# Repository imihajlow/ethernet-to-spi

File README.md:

# An experiment project to receive and decode a 10BASE-T Ethernet signal

The Nucleo64 shield schematic files are located in sch/shield/.

The firmware for stm32f401 is located in stm32eth-f401/.

## Receiver operation

The idea is to convert the Manchester-encoded 10BASE-T signal to SPI and use an STM32 MCU to parse it.

A 75C1168 chip is used to convert differential signals to 5V logic levels.

Then, edges are detected using a 74HC86 XOR.

*Blue is the input signal, yellow - detected edges.*

Then, an `~idle` signal is formed using a delay circuit. It goes from 0 to 1 with the first edge and goes back to 0 after approximately 2 µS after the last transition. This signal is used by the MCU to detect the end of an Ethernet frame.

When the line is idle, the output of an 75C1168 is undefined. In my case it was always high. Since the Ethernet frame always starts with a pattern of 101010..., this leads to the first transition always being from 1 to 0, which generates the first edge. This edge must be ignored for SPI clock generation. However, the case with a low idle state needs to be handled as well. In that case the line remains low on the frame begin and the first edge should not be ignored.

The filtering of the first edge is done using the already generated `~idle` signal.

*First edge is filtered*

The resulting filtered edge signal is fed onto a non-retriggerable monostable circuit which generates a pulse of approximately 75 nS, which is finally used as an SPI clock.

*Blue - generated SPI SCK signal, yellow - SPI MOSI which is just the input 10BASE-T signal.*

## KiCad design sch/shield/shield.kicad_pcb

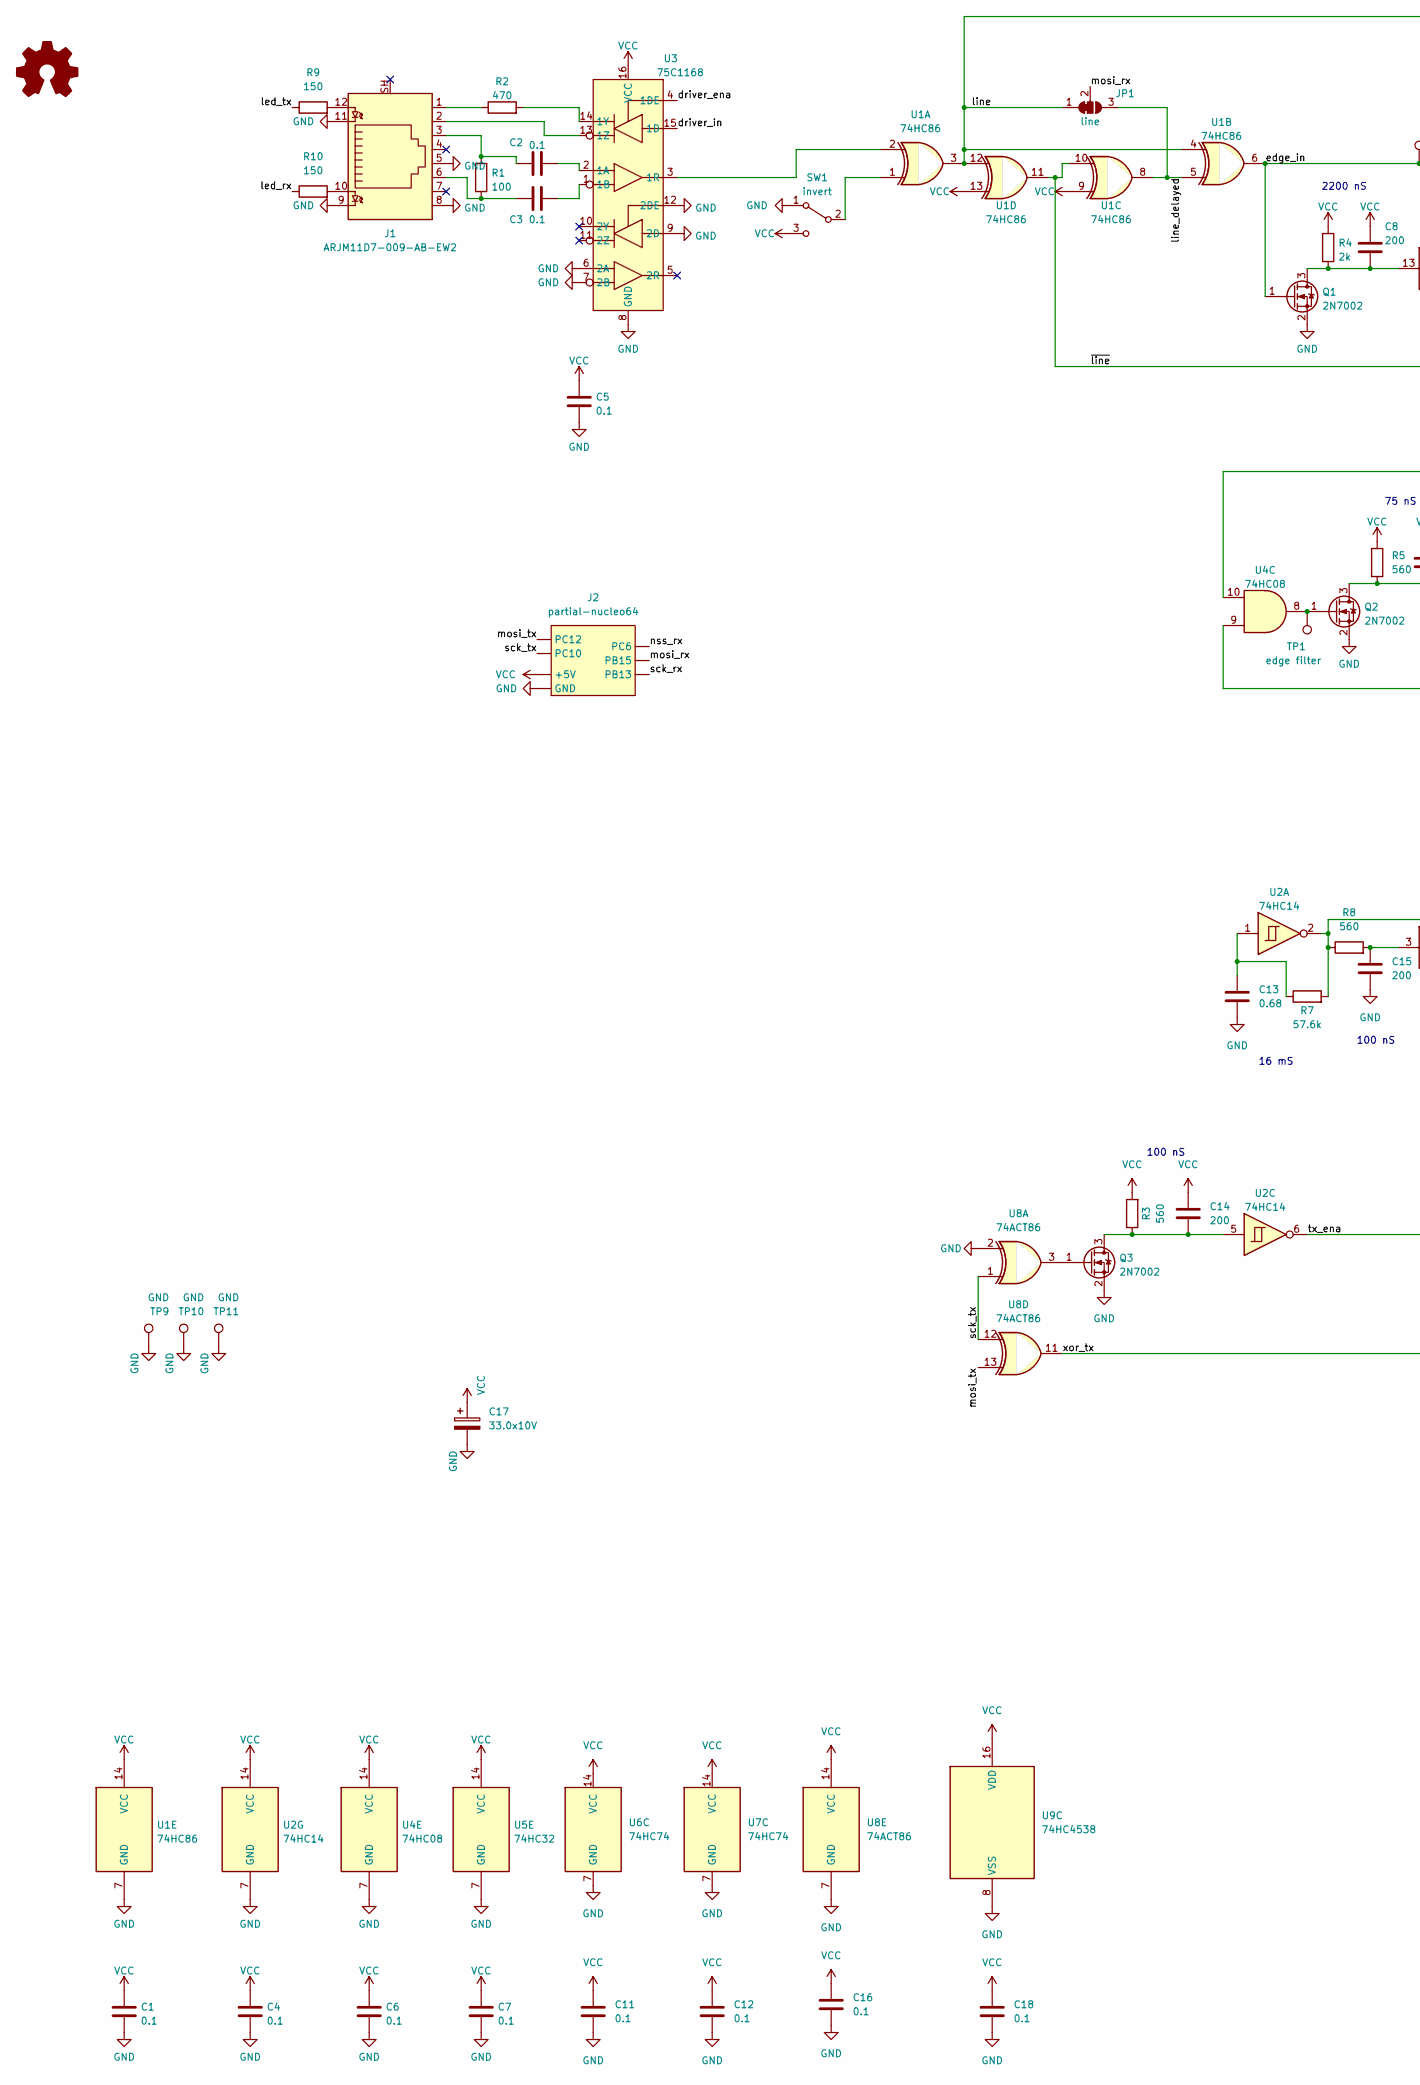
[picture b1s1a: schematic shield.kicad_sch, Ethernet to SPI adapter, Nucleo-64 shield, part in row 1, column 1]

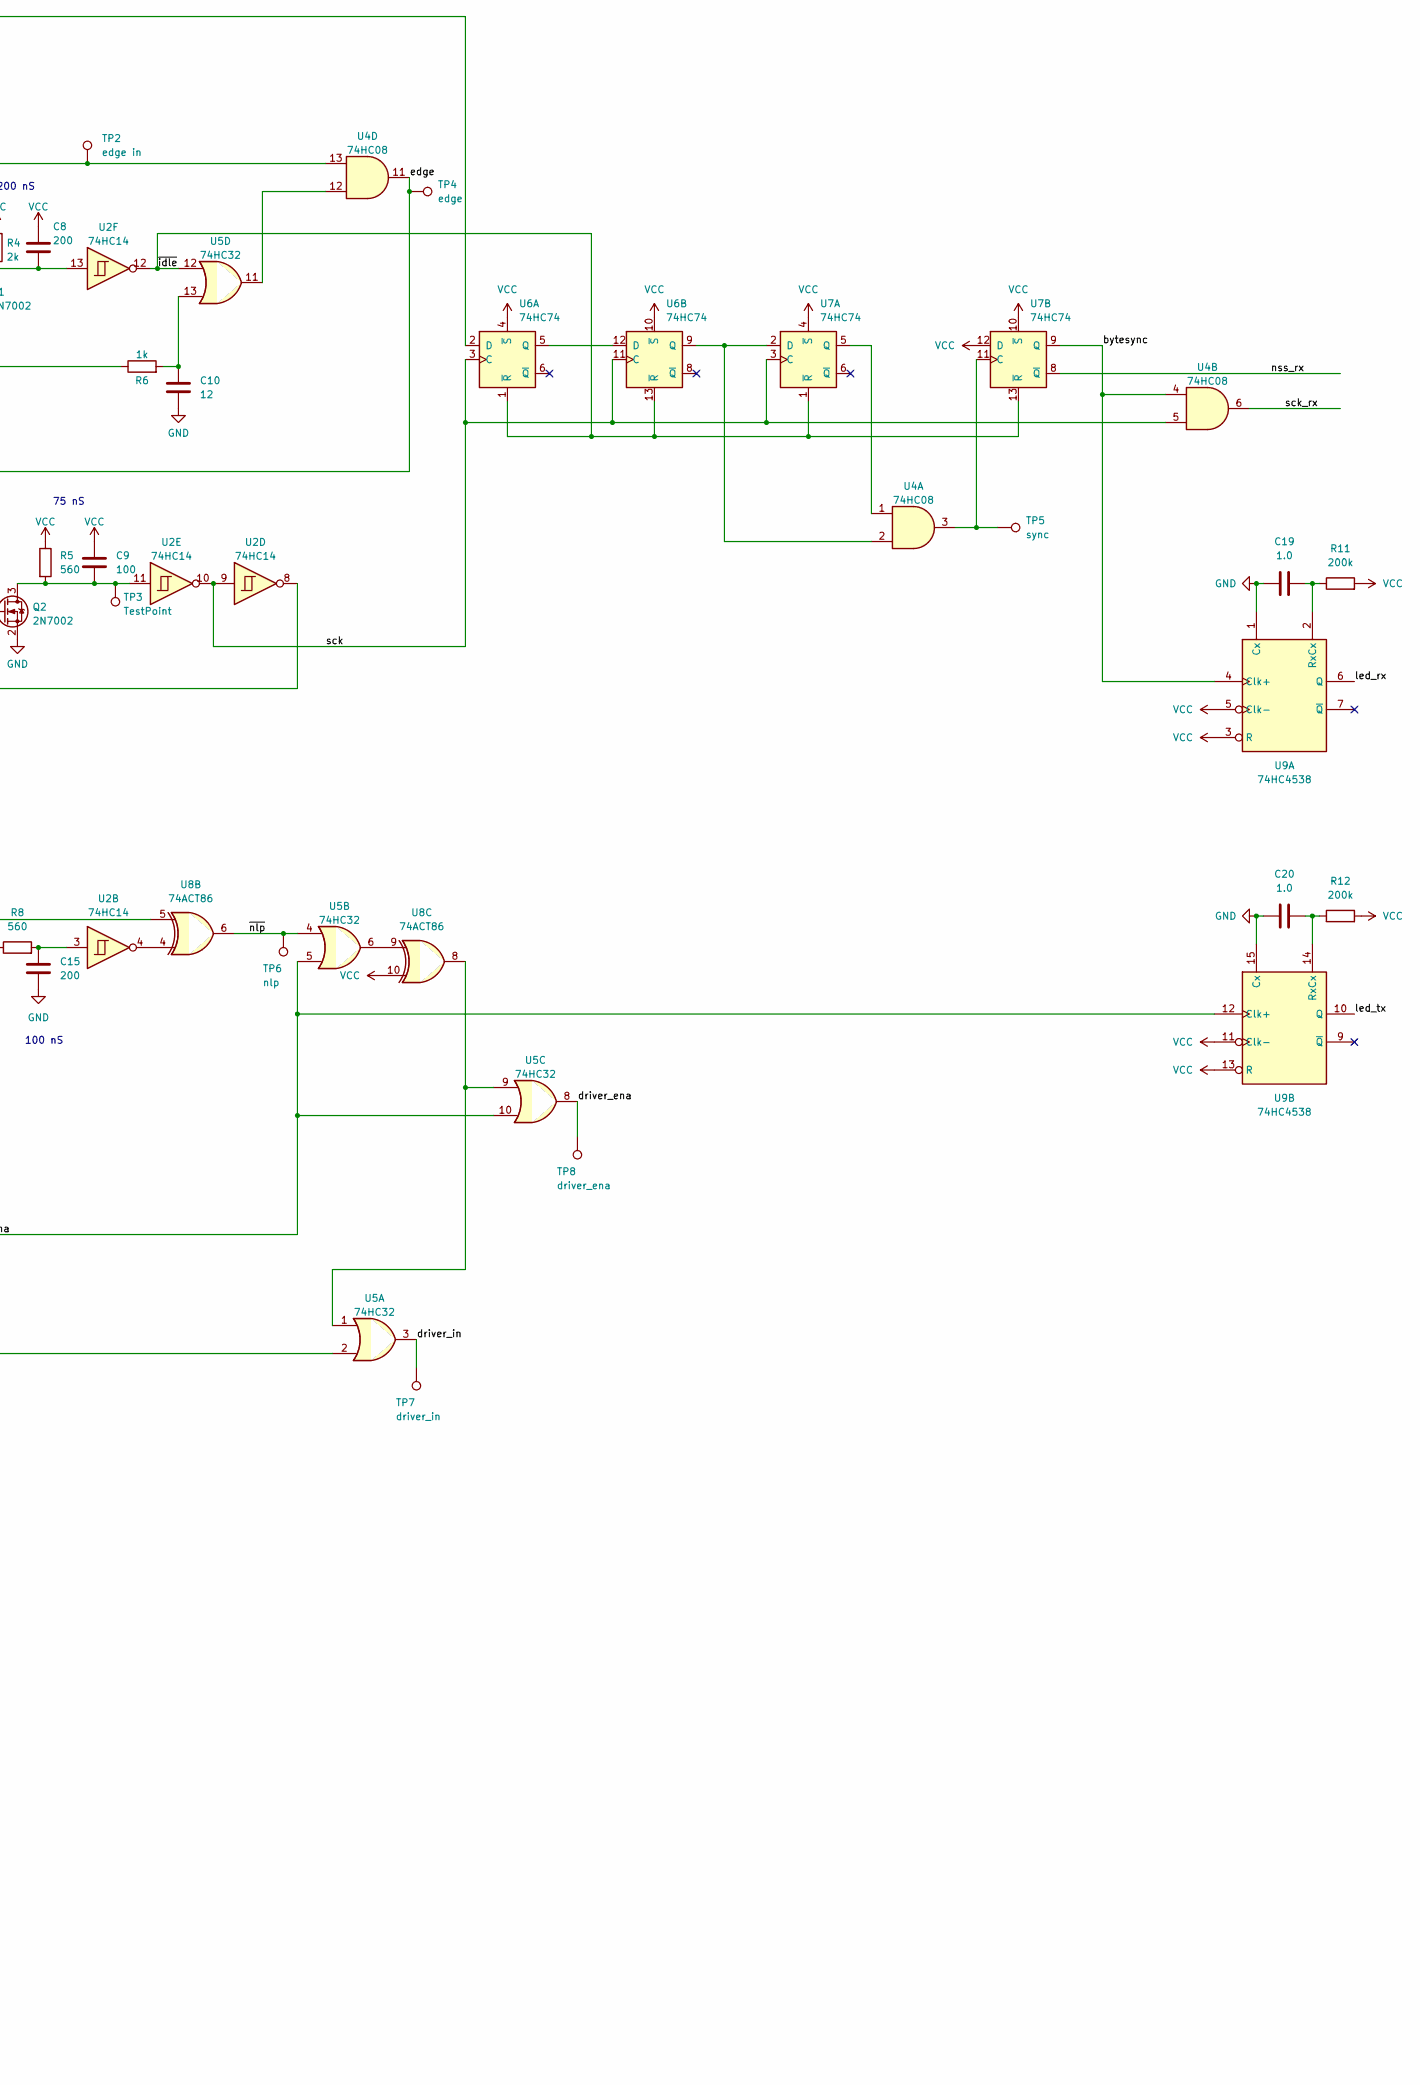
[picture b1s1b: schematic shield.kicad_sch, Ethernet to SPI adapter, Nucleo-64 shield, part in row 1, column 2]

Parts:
C1, C2, C3, C4, C5, C6, C7, C11, C12, C16, C18: 0.1; C_0805_2012Metric
C8, C14, C15: 200; C_0805_2012Metric
C9: 100; C_0805_2012Metric
C10: 12; C_0805_2012Metric
C13: 0.68; C_0805_2012Metric
C17: 33.0x10V; C_1210_3225Metric
C19, C20: 1.0; C_0805_2012Metric
J1: ARJM11D7-009-AB-EW2; ARJM11D7-009
J2: partial-nucleo64
JP1: line; SolderJumper-3_P1.3mm_Open_RoundedPad1.0x1.5mm
Q1, Q2, Q3: 2N7002; SOT-23
R1: 100; R_0805_2012Metric
R2: 470; R_0805_2012Metric
R3, R5, R8: 560; R_0805_2012Metric
R4: 2k; R_0805_2012Metric
R6: 1k; R_0805_2012Metric
R7: 57.6k; R_0805_2012Metric
R9, R10: 150; R_0805_2012Metric
R11, R12: 200k; R_0805_2012Metric
SW1: invert; SW_Slide_1P2T_CK_OS102011MS2Q
TP1: edge filter; TestPoint_Pad_D1.5mm
TP2: edge in; TestPoint_Pad_D1.5mm
TP3: TestPoint; TestPoint_Pad_D1.5mm
TP4: edge; TestPoint_Pad_D1.5mm
TP5: sync; TestPoint_Pad_D1.5mm
TP6: nlp; TestPoint_Pad_D1.5mm
TP7: driver_in; TestPoint_Pad_D1.5mm
TP8: driver_ena; TestPoint_Pad_D1.5mm
TP9, TP10, TP11: GND; TestPoint_Pad_D1.5mm
U1: 74HC86; SOIC-14_3.9x8.7mm_P1.27mm
U2: 74HC14; TSSOP-14_4.4x5mm_P0.65mm
U3: 75C1168; TSSOP-16_4.4x5mm_P0.65mm
U4: 74HC08; TSSOP-14_4.4x5mm_P0.65mm
U5: 74HC32; SOIC-14_3.9x8.7mm_P1.27mm
U6, U7: 74HC74; TSSOP-14_4.4x5mm_P0.65mm
U8: 74ACT86; SOIC-14_3.9x8.7mm_P1.27mm
U9: 74HC4538; SOIC-16_4.55x10.3mm_P1.27mm

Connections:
/bytesync: U4.4, U7.9 (Q), U9.4 (Clk+)
/driver_ena: TP8.1, U3.4 (1DE), U5.8
/driver_in: TP7.1, U3.15 (1D), U5.3
/edge: TP4.1, U4.10, U4.11
/edge_in: Q1.1 (G), TP2.1, U1.6, U4.13
/led_rx: R10.1, U9.6 (Q)
/led_tx: R9.1, U9.10 (Q)
/line: JP1.1 (A), U1.3, U1.4, U1.12, U6.2 (D)
/line_delayed: JP1.3 (B), U1.5, U1.8
/mosi_rx: J2.PB15, JP1.2 (C)
/mosi_tx: J2.PC12, U8.13
/nss_rx: J2.PC6, U7.8 (~Q)
/sck: U2.9, U2.10, U4.5, U6.3 (C), U6.11 (C), U7.3 (C)
/sck_rx: J2.PB13, U4.6
/sck_tx: J2.PC10, U8.1, U8.12
/tx_ena: U2.6, U5.5, U5.10, U9.12 (Clk+)
/xor_tx: U5.2, U8.11
/~idle: U2.12, U5.12, U6.1 (~R), U6.13 (~R), U7.1 (~R), U7.13 (~R)
/~line: R6.1, U1.10, U1.11
/~nlp: TP6.1, U5.4, U8.6
GND: C1.2, C4.2, C5.2, C6.2, C7.2, C10.2, C11.2, C12.2, C13.2, C15.2, C16.2, C17.2, C18.2, C19.1, C20.1, J1.5, J1.8, J1.9, J1.11, J2.GND, Q1.2 (S), Q2.2 (S), Q3.2 (S), SW1.1 (A), TP9.1, TP10.1, TP11.1, U1.7 (GND), U2.7 (GND), U3.6 (2A), U3.7 (2B), U3.8 (GND), U3.9 (2D), U3.12 (2DE), U4.7 (GND), U5.7 (GND), U6.7 (GND), U7.7 (GND), U8.2, U8.7 (GND), U9.1 (Cx), U9.8 (VSS), U9.15 (Cx)
unnamed: C2.1, J1.3, R1.1
unnamed: C2.2, U3.2 (1A)
unnamed: C3.1, J1.6, R1.2
unnamed: C3.2, U3.1 (1B)
unnamed: C8.2, Q1.3 (D), R4.2, U2.13
unnamed: C9.2, Q2.3 (D), R5.2, TP3.1, U2.11
unnamed: C10.1, R6.2, U5.13
unnamed: C13.1, R7.1, U2.1
unnamed: C14.2, Q3.3 (D), R3.1, U2.5
unnamed: C15.1, R8.2, U2.3
unnamed: C19.2, R11.1, U9.2 (RxCx)
unnamed: C20.2, R12.1, U9.14 (RxCx)
unnamed: J1.1, R2.1
unnamed: J1.2, U3.13 (1Z)
unnamed: J1.10, R10.2
unnamed: J1.12, R9.2
unnamed: Q2.1 (G), TP1.1, U4.8
unnamed: Q3.1 (G), U8.3
unnamed: R2.2, U3.14 (1Y)
unnamed: R7.2, R8.1, U2.2, U8.5
unnamed: SW1.2 (B), U1.1
unnamed: TP5.1, U4.3, U7.11 (C)
unnamed: U1.2, U3.3 (1R)
unnamed: U2.4, U8.4
unnamed: U2.8, U4.9
unnamed: U4.1, U7.5 (Q)
unnamed: U4.2, U6.9 (Q), U7.2 (D)
unnamed: U4.12, U5.11
unnamed: U5.1, U5.9, U8.8
unnamed: U5.6, U8.9
unnamed: U6.5 (Q), U6.12 (D)
VCC: C1.1, C4.1, C5.1, C6.1, C7.1, C8.1, C9.1, C11.1, C12.1, C14.1, C16.1, C17.1, C18.1, J2.+5V, R3.2, R4.1, R5.1, R11.2, R12.2, SW1.3 (C), U1.9, U1.13, U1.14 (VCC), U2.14 (VCC), U3.16 (VCC), U4.14 (VCC), U5.14 (VCC), U6.4 (~S), U6.10 (~S), U6.14 (VCC), U7.4 (~S), U7.10 (~S), U7.12 (D), U7.14 (VCC), U8.10, U8.14 (VCC), U9.3 (R), U9.5 (Clk-), U9.11 (Clk-), U9.13 (R), U9.16 (VDD)

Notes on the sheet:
2200 nS
100 nS
16 mS
75 nS

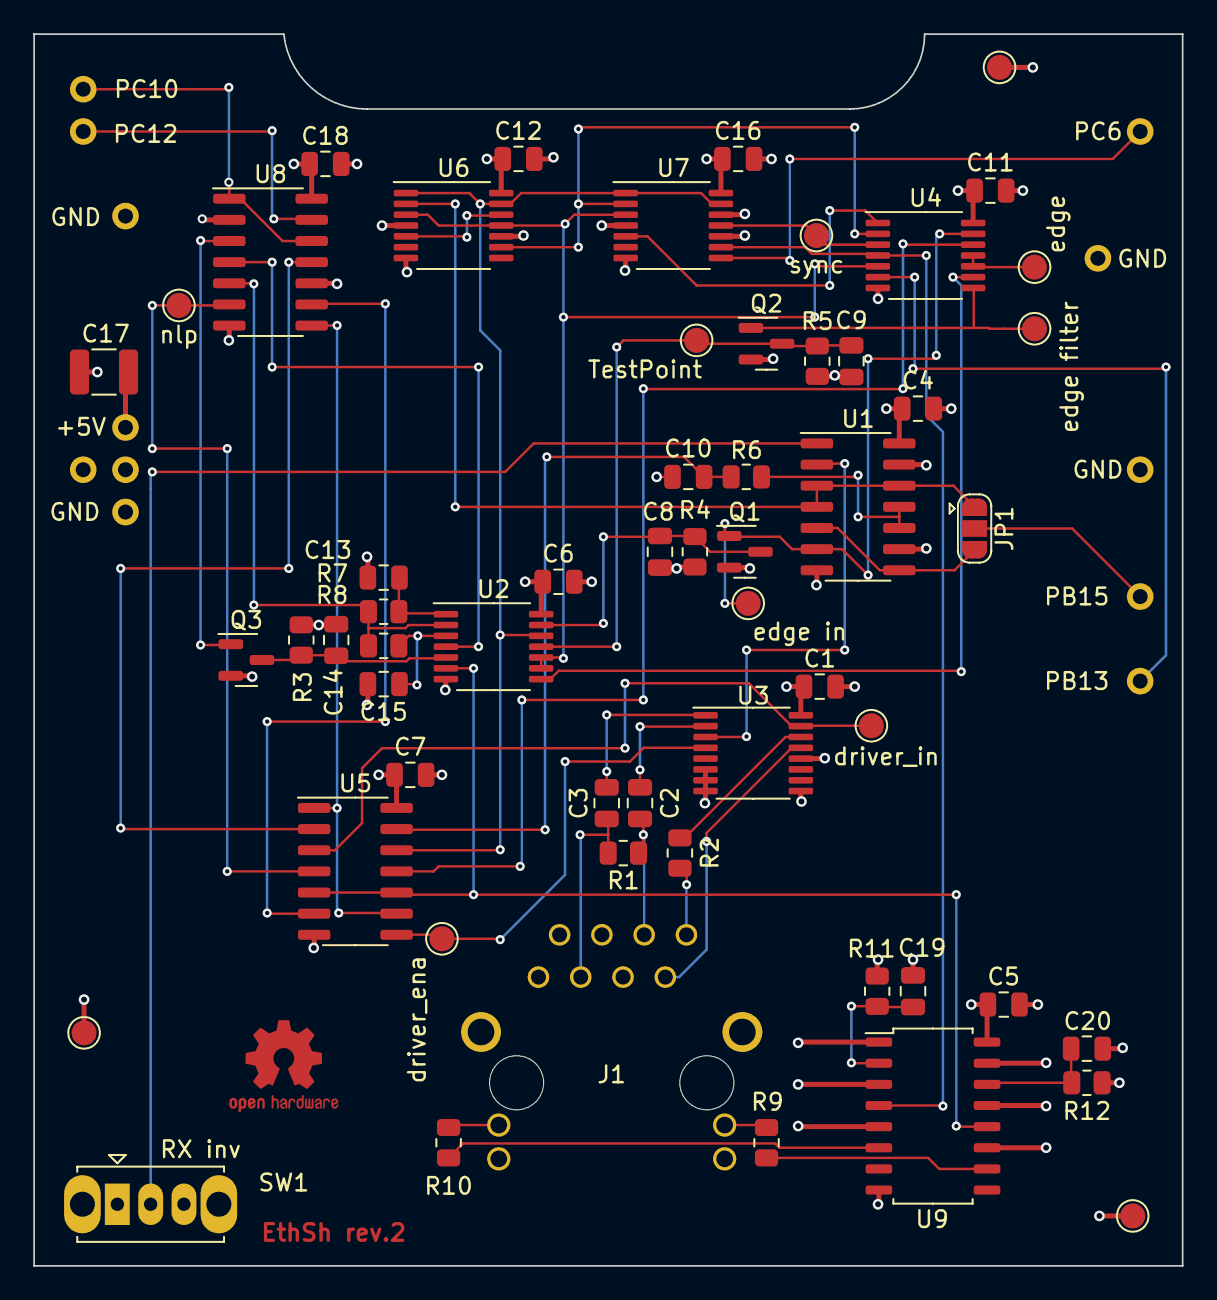
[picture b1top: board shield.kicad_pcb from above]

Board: 4 copper layers, 69.0 x 74.0 mm, 59 parts (0 on the bottom side), 53 nets.

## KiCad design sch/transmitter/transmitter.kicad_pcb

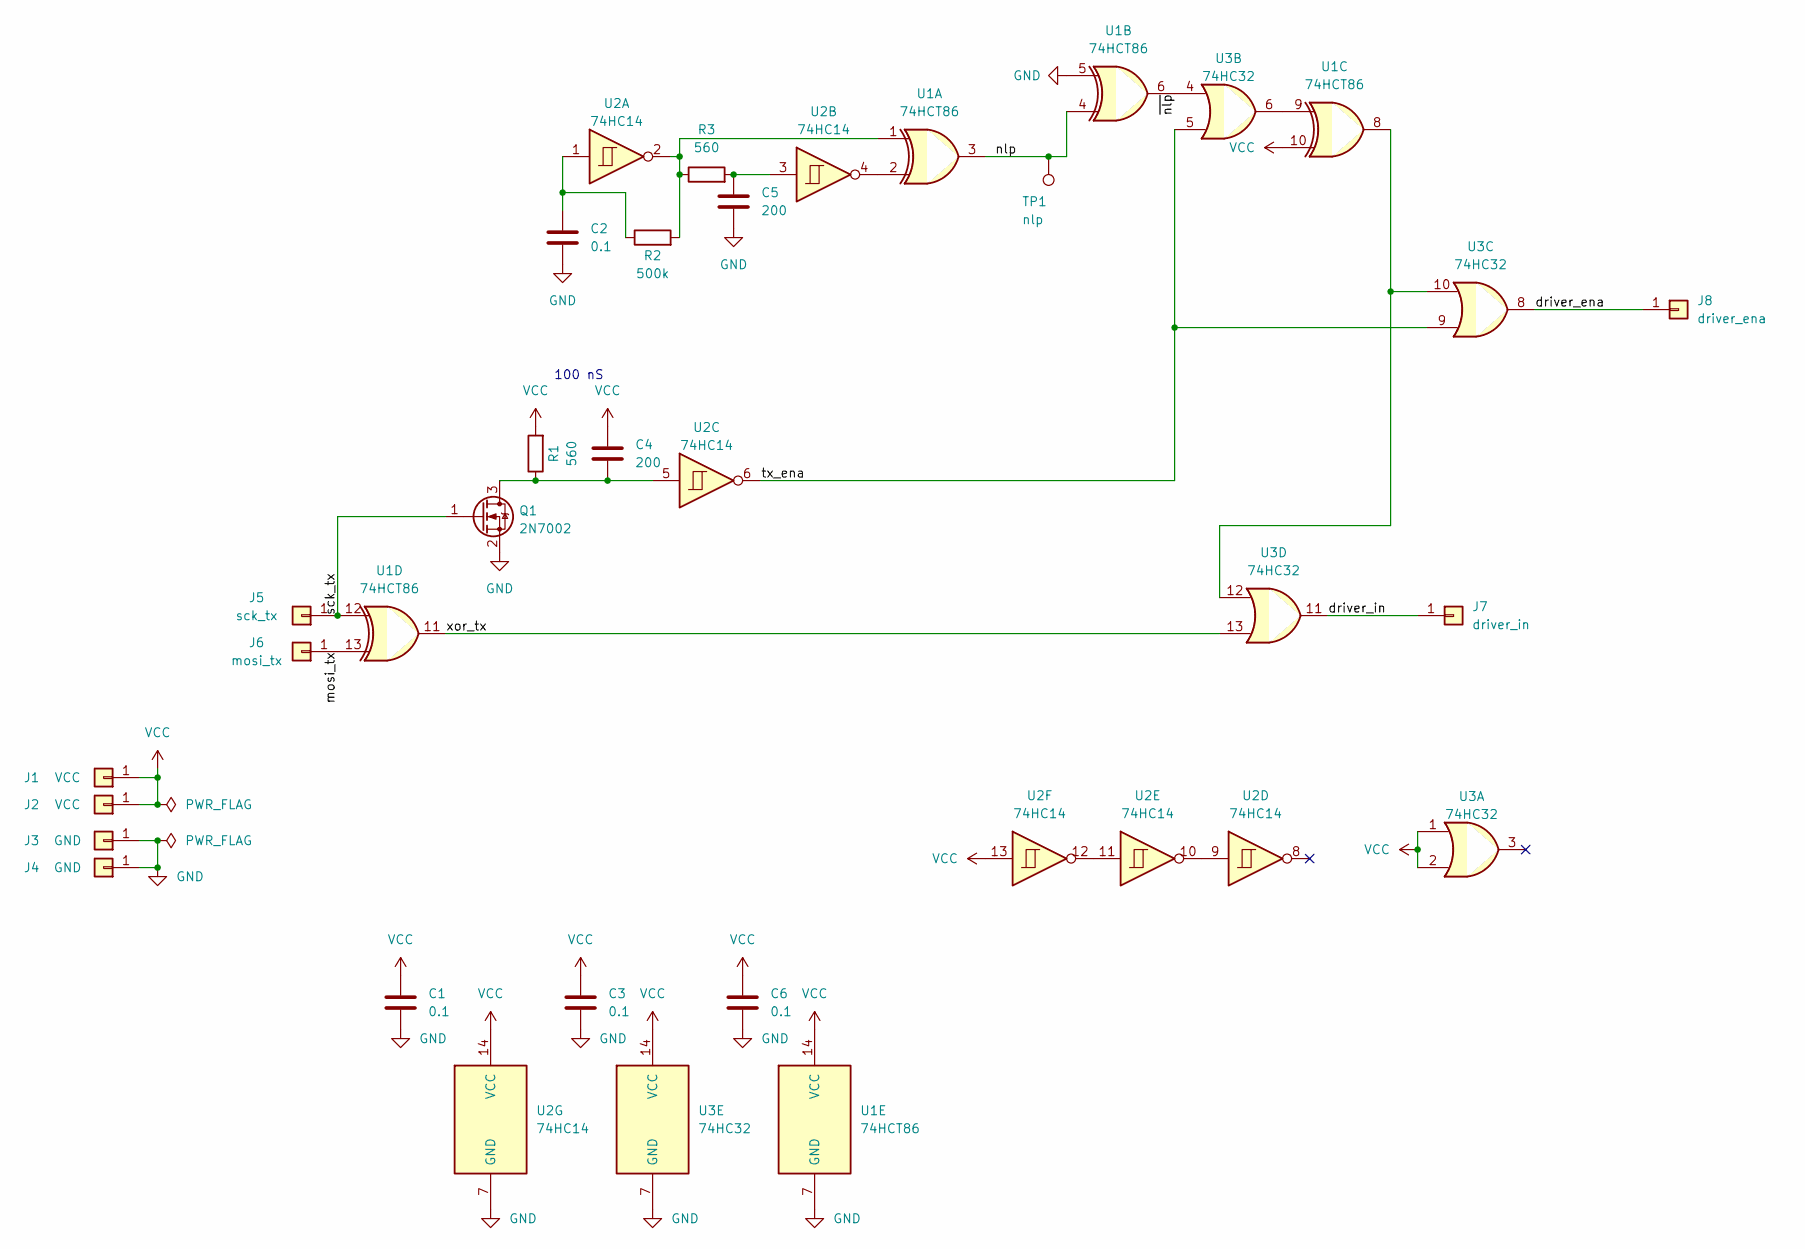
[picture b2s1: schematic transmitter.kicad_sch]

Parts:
C1, C3, C6: 0.1; C_0805_2012Metric
C2: 0.1; C_Disc_D4.3mm_W1.9mm_P5.00mm
C4, C5: 200; C_0805_2012Metric
J1, J2: VCC; SolderWire-0.5sqmm_1x01_D0.9mm_OD2.3mm_Relief
J3, J4: GND; SolderWire-0.5sqmm_1x01_D0.9mm_OD2.3mm_Relief
J5: sck_tx; SolderWire-0.5sqmm_1x01_D0.9mm_OD2.3mm_Relief
J6: mosi_tx; SolderWire-0.5sqmm_1x01_D0.9mm_OD2.3mm_Relief
J7: driver_in; SolderWire-0.5sqmm_1x01_D0.9mm_OD2.3mm_Relief
J8: driver_ena; SolderWire-0.5sqmm_1x01_D0.9mm_OD2.3mm_Relief
Q1: 2N7002; SOT-23
R1, R3: 560; R_0805_2012Metric
R2: 500k; R_Axial_DIN0207_L6.3mm_D2.5mm_P7.62mm_Horizontal
TP1: nlp; TestPoint_Pad_D3.0mm
U1: 74HCT86; DIP-14_W7.62mm
U2: 74HC14; SOIC-14_3.9x8.7mm_P1.27mm
U3: 74HC32; SOIC-14_3.9x8.7mm_P1.27mm

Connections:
/driver_ena: J8.1, U3.8
/driver_in: J7.1, U3.11
/mosi_tx: J6.1, U1.13
/nlp: TP1.1, U1.3, U1.4
/sck_tx: J5.1, Q1.1 (G), U1.12
/tx_ena: U2.6, U3.5, U3.9
/xor_tx: U1.11, U3.13
/~nlp: U1.6, U3.4
GND: C1.2, C2.2, C3.2, C5.2, C6.2, J3.1, J4.1, Q1.2 (S), U1.5, U1.7 (GND), U2.7 (GND), U3.7 (GND)
unnamed: C2.1, R2.1, U2.1
unnamed: C4.2, Q1.3 (D), R1.1, U2.5
unnamed: C5.1, R3.2, U2.3
unnamed: R2.2, R3.1, U1.1, U2.2
unnamed: U1.2, U2.4
unnamed: U1.8, U3.10, U3.12
unnamed: U1.9, U3.6
unnamed: U2.9, U2.10
unnamed: U2.11, U2.12
VCC: C1.1, C3.1, C4.1, C6.1, J1.1, J2.1, R1.2, U1.10, U1.14 (VCC), U2.13, U2.14 (VCC), U3.1, U3.2, U3.14 (VCC)

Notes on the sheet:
100 nS

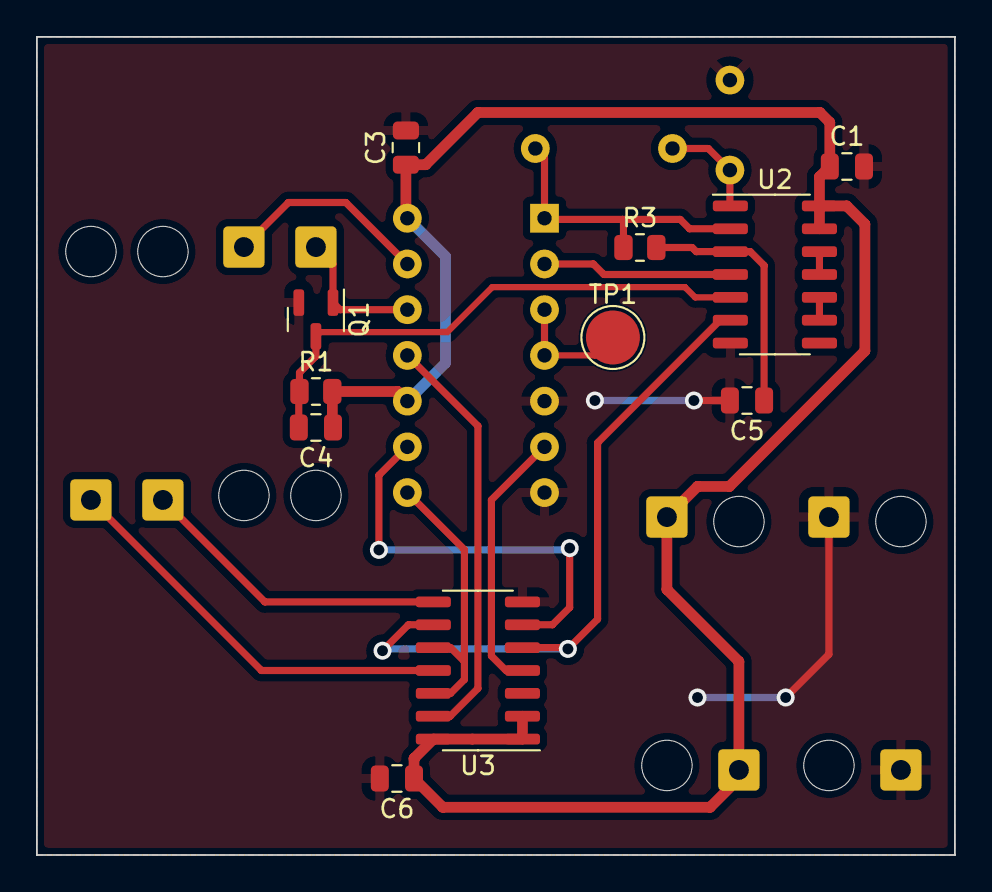
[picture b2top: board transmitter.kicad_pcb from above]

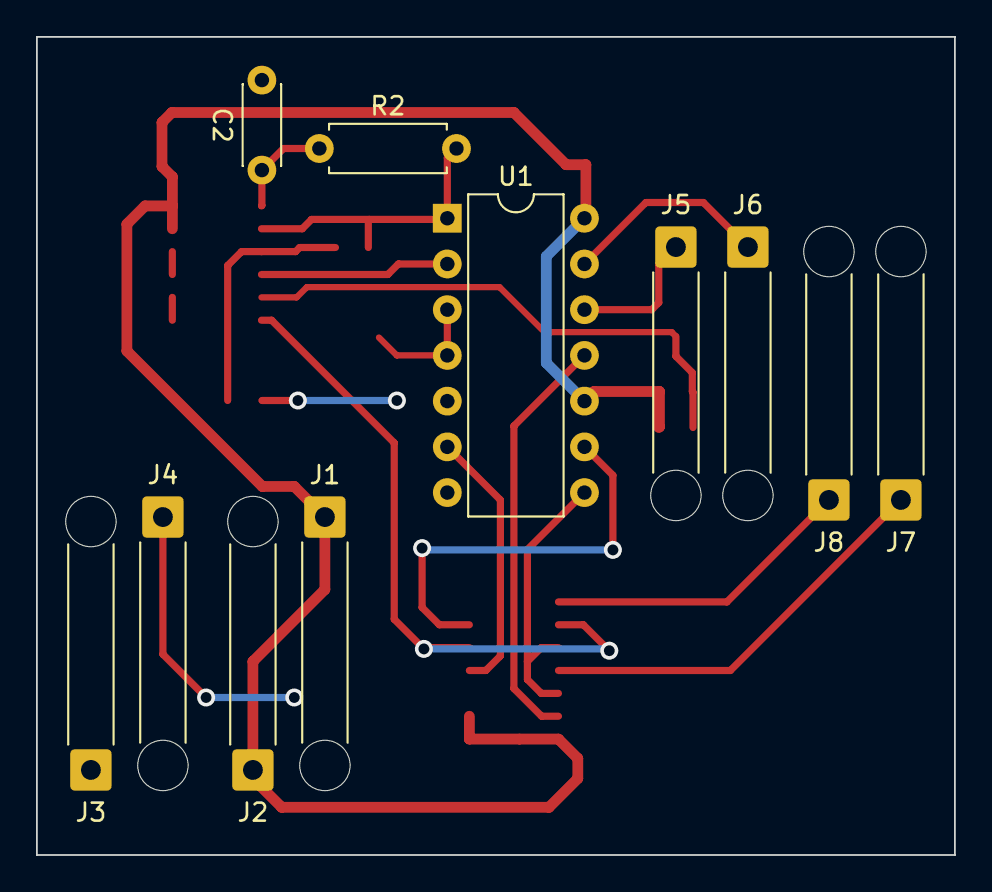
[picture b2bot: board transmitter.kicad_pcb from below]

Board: 2 copper layers, 51.0 x 45.5 mm, 22 parts (11 on the bottom side), 19 nets.

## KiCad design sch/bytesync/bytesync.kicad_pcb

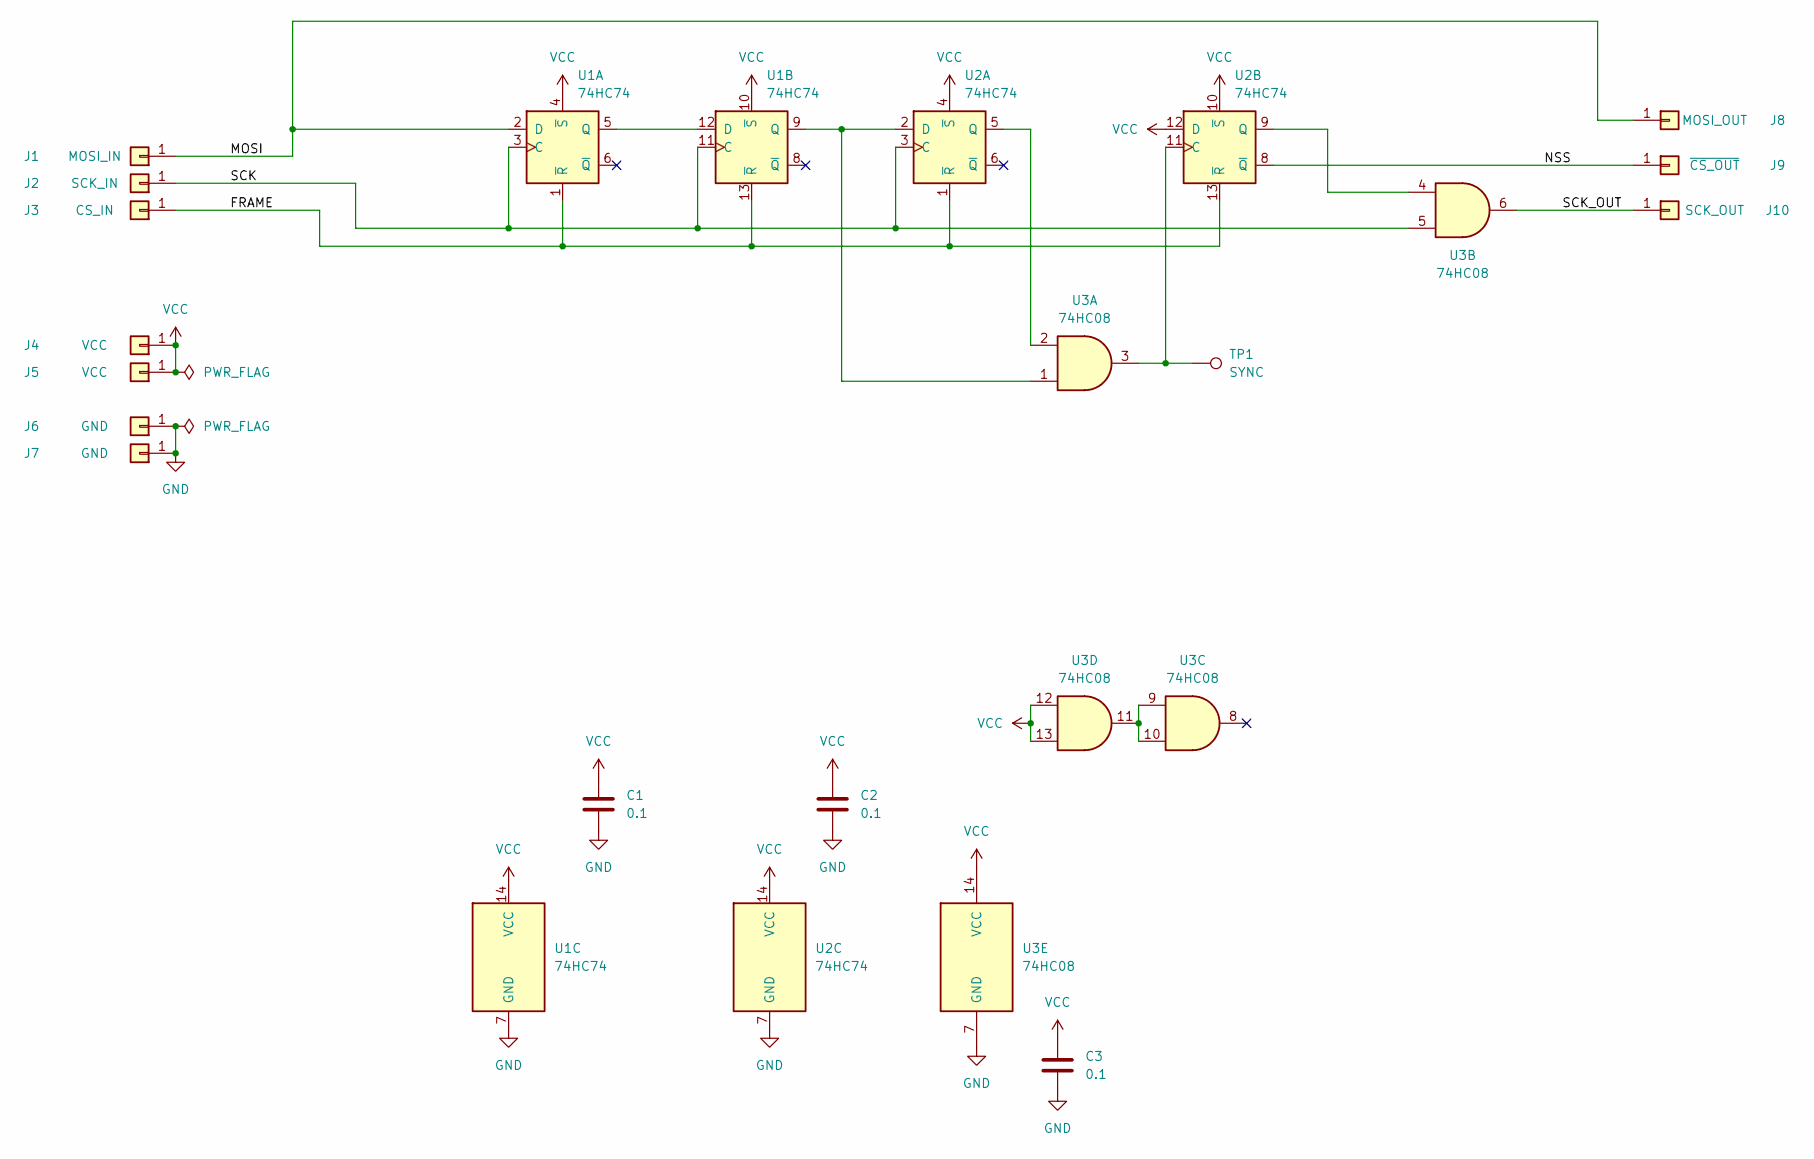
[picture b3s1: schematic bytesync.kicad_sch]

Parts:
C1, C2, C3: 0.1; C_0805_2012Metric
J1: MOSI_IN; SolderWire-0.75sqmm_1x01_D1.25mm_OD2.3mm_Relief
J2: SCK_IN; SolderWire-0.75sqmm_1x01_D1.25mm_OD2.3mm_Relief
J3: CS_IN; SolderWire-0.75sqmm_1x01_D1.25mm_OD2.3mm_Relief
J4, J5: VCC; SolderWire-0.75sqmm_1x01_D1.25mm_OD2.3mm_Relief
J6, J7: GND; SolderWire-0.75sqmm_1x01_D1.25mm_OD2.3mm_Relief
J8: MOSI_OUT; SolderWire-0.75sqmm_1x01_D1.25mm_OD2.3mm_Relief
J9: ~{CS_OUT}; SolderWire-0.75sqmm_1x01_D1.25mm_OD2.3mm_Relief
J10: SCK_OUT; SolderWire-0.75sqmm_1x01_D1.25mm_OD2.3mm_Relief
TP1: SYNC; TestPoint_Pad_D2.0mm
U1, U2: 74HC74; SOIC-14_3.9x8.7mm_P1.27mm
U3: 74HC08; SOIC-14_3.9x8.7mm_P1.27mm

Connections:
/FRAME: J3.1, U1.1 (~R), U1.13 (~R), U2.1 (~R), U2.13 (~R)
/MOSI: J1.1, J8.1, U1.2 (D)
/NSS: J9.1, U2.8 (~Q)
/SCK: J2.1, U1.3 (C), U1.11 (C), U2.3 (C), U3.5
/SCK_OUT: J10.1, U3.6
GND: C1.2, C2.2, C3.2, J6.1, J7.1, U1.7 (GND), U2.7 (GND), U3.7 (GND)
unnamed: TP1.1, U2.11 (C), U3.3
unnamed: U1.9 (Q), U2.2 (D), U3.1
unnamed: U1.5 (Q), U1.12 (D)
unnamed: U2.5 (Q), U3.2
unnamed: U2.9 (Q), U3.4
unnamed: U3.9, U3.10, U3.11
VCC: C1.1, C2.1, C3.1, J4.1, J5.1, U1.4 (~S), U1.10 (~S), U1.14 (VCC), U2.4 (~S), U2.10 (~S), U2.12 (D), U2.14 (VCC), U3.12, U3.13, U3.14 (VCC)

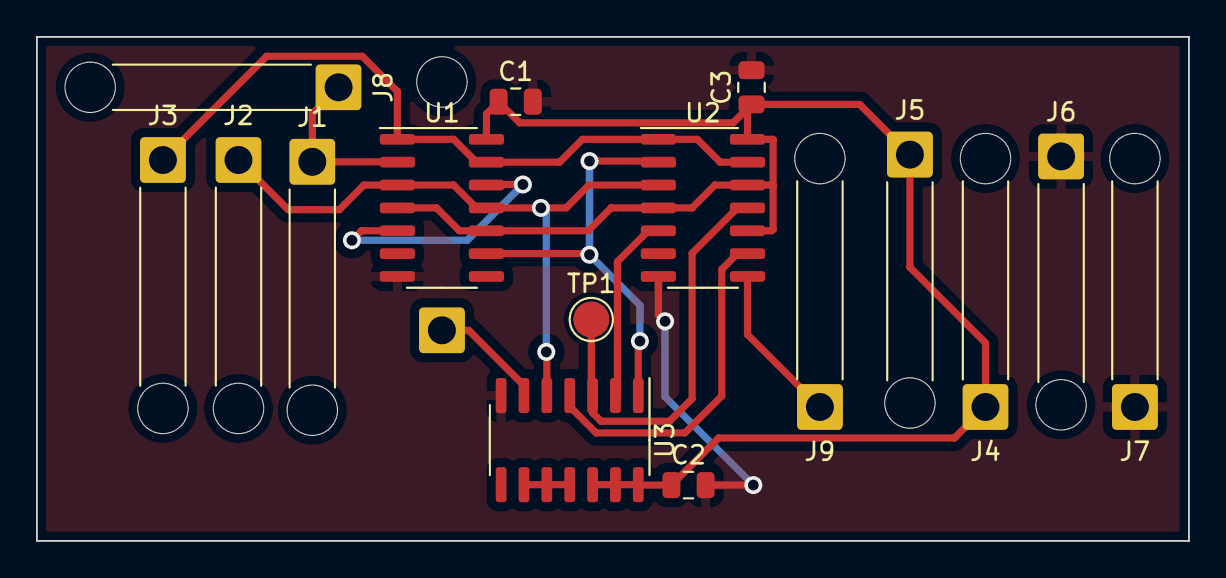
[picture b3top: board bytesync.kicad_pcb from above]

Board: 2 copper layers, 64.0 x 28.0 mm, 17 parts (1 on the bottom side), 13 nets.

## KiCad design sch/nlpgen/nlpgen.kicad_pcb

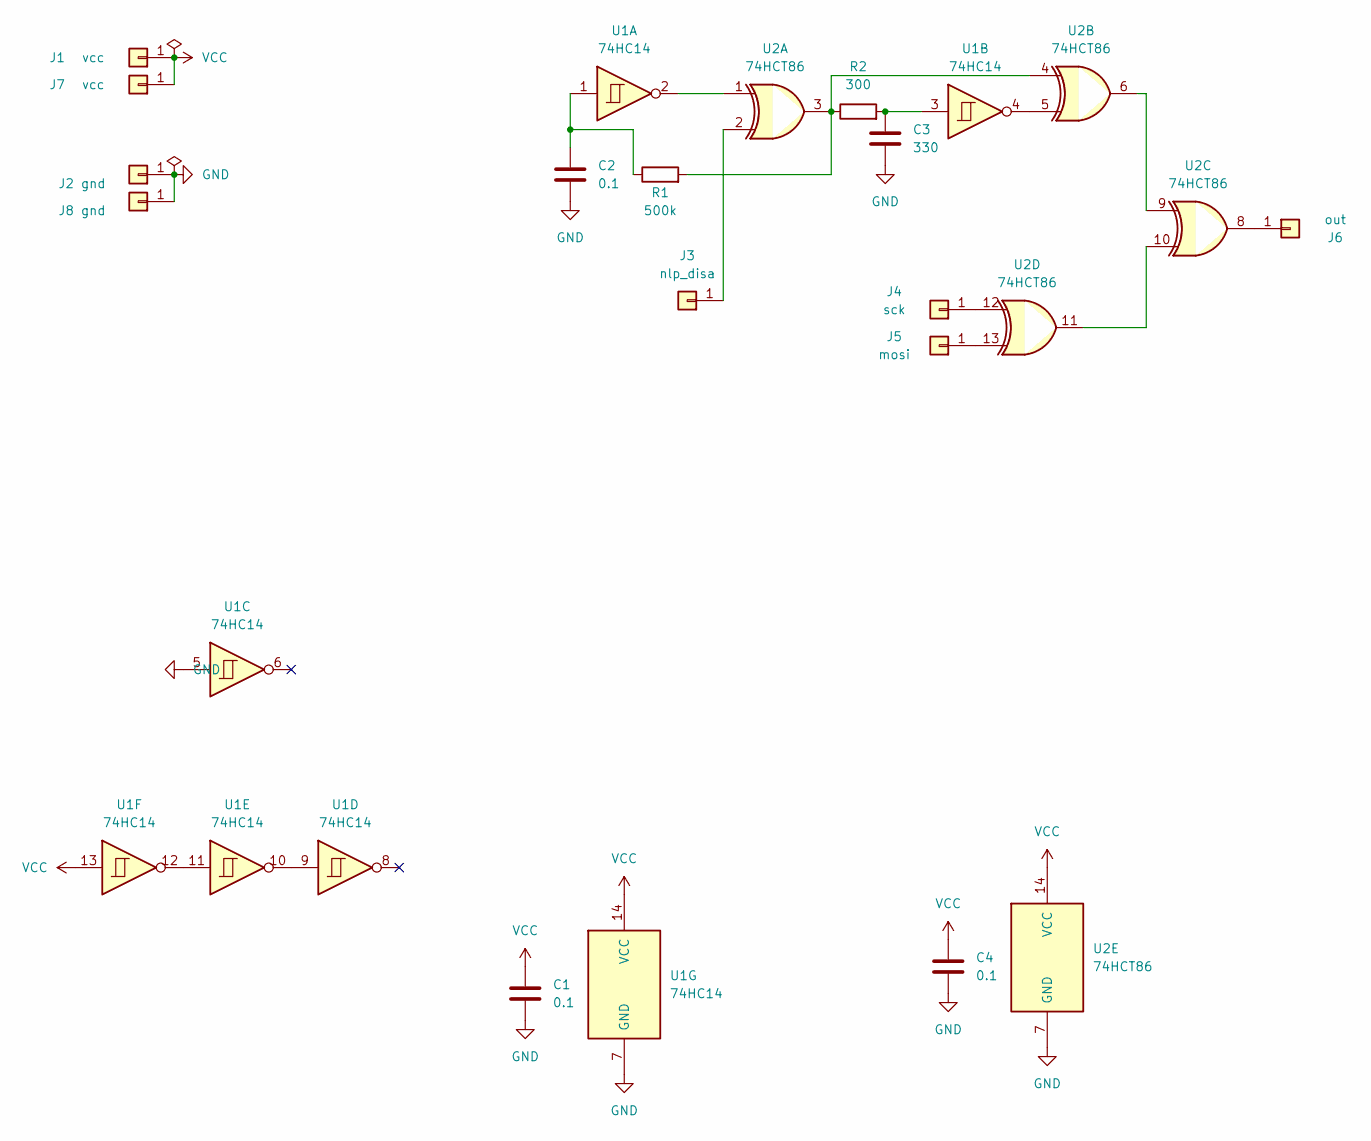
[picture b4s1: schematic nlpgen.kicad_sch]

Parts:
C1, C2, C4: 0.1; C_0805_2012Metric
C3: 330; C_0805_2012Metric
J1, J7: vcc; SolderWire-0.5sqmm_1x01_D0.9mm_OD2.3mm_Relief
J2, J8: gnd; SolderWire-0.5sqmm_1x01_D0.9mm_OD2.3mm_Relief
J3: nlp_disa; SolderWire-0.5sqmm_1x01_D0.9mm_OD2.3mm_Relief
J4: sck; SolderWire-0.5sqmm_1x01_D0.9mm_OD2.3mm_Relief
J5: mosi; SolderWire-0.5sqmm_1x01_D0.9mm_OD2.3mm_Relief
J6: out; SolderWire-0.5sqmm_1x01_D0.9mm_OD2.3mm_Relief
R1: 500k; R_Axial_DIN0204_L3.6mm_D1.6mm_P7.62mm_Horizontal
R2: 300; R_0805_2012Metric
U1: 74HC14; SOIC-14_3.9x8.7mm_P1.27mm
U2: 74HCT86; DIP-14_W7.62mm

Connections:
GND: C1.2, C2.2, C3.2, C4.2, J2.1, J8.1, U1.5, U1.7 (GND), U2.7 (GND)
unnamed: C2.1, R1.1, U1.1
unnamed: C3.1, R2.2, U1.3
unnamed: U1.4, U2.5
unnamed: U1.9, U1.10
unnamed: U1.11, U1.12
unnamed: U1.2, U2.1
unnamed: J3.1, U2.2
unnamed: R1.2, R2.1, U2.3, U2.4
unnamed: J6.1, U2.8
unnamed: U2.6, U2.9
unnamed: U2.10, U2.11
unnamed: J4.1, U2.12
unnamed: J5.1, U2.13
VCC: C1.1, C4.1, J1.1, J7.1, U1.13, U1.14 (VCC), U2.14 (VCC)

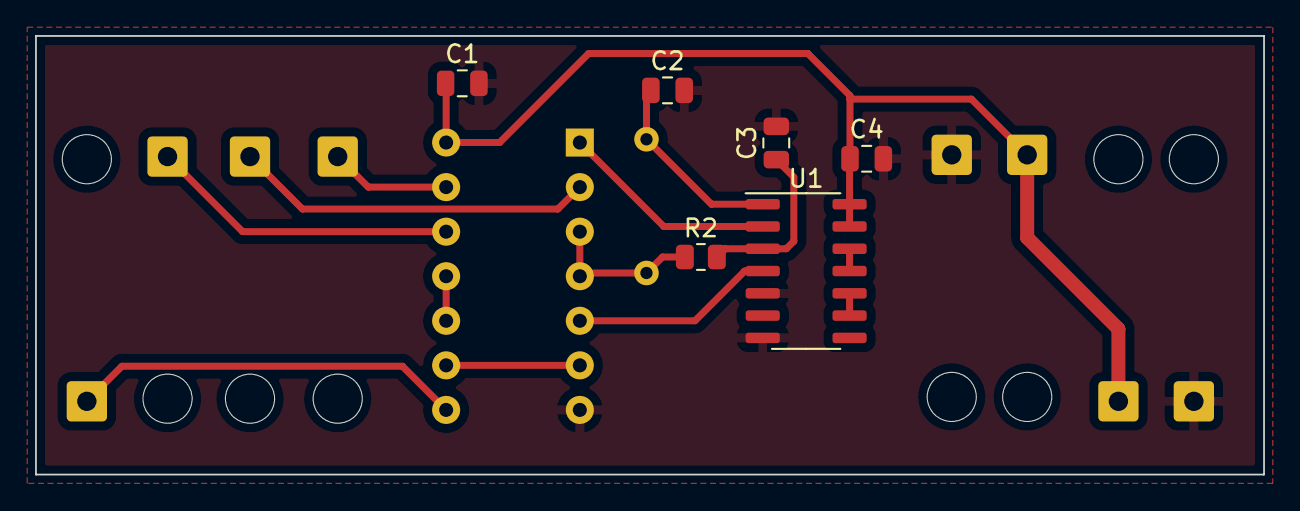
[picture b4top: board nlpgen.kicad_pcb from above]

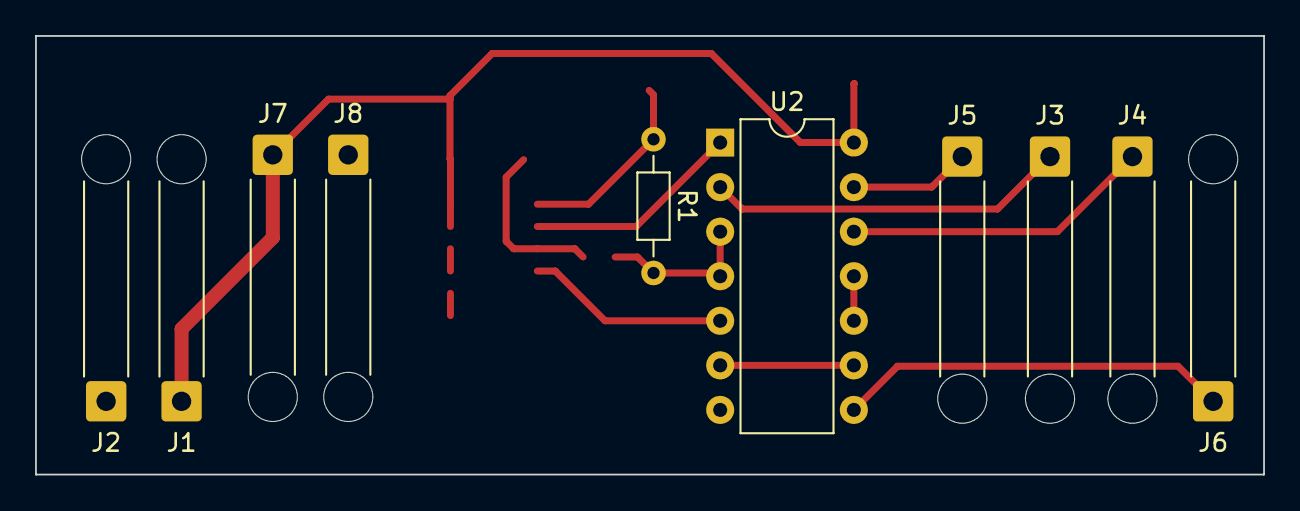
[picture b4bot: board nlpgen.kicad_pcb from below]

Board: 2 copper layers, 70.0 x 25.0 mm, 16 parts (10 on the bottom side), 15 nets.

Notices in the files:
sch/shield/shield.kicad_pcb:
Licensed under the TAPR Open Hardware License (www.tapr.org/OHL)
Licensed under the TAPR OHL
